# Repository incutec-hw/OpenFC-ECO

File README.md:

# OpenFC-Lite-Mini

Open-source Betaflight flight controller — **20×20 mm**, 6-layer, 3S–6S, built around the RP2354B microcontroller. Compact and low-cost: external RX over UART, microSD blackbox, analog OSD.

> This repository is the **Mini** (20×20). A larger **OpenFC-Lite** (30.5×30.5 mm, bigger pads, more I/O, full-size SD) will be derived from this design once the Mini is finalized.

## At a glance

| | |
|---|---|
| MCU | RP2354B — dual Cortex-M33 @ 150 MHz, 2 MB flash, QFN-80 |
| IMU | 6-axis, SPI0 (LGA-14 footprint — part TBD, see [IMU](#imu)) |
| Blackbox | microSD card slot (TF-021B-H265) on SPI1 |
| OSD | analog, PIO-driven (sync separator + op-amp + SPDT switch) |
| Power | 3S–6S; switchable 10V (VTX/cam) + always-on 5V |
| Size | 20×20 mm, 6-layer |
| RX | external, over UART |
| USB | USB-C, USB-CDC for configuration |

Intentionally omitted to keep it small and cheap: barometer, integrated ELRS receiver, onboard WS2812B LEDs (LED-strip pad only), onboard SPI blackbox flash (microSD instead).

## Status

Rev 1 boards have been received and brought up. The custom Betaflight target builds and flashes; USB enumeration, IMU, SD card blackbox, and the switchable 10V VTX rail are confirmed working on bench. Bring-up of motors, external RX, and the analog OSD chain is in progress. See the [Rev 2 Change List](#rev-2-change-list) for hardware fixes scheduled for the next revision.

## Specifications

### Core
- **MCU:** RP2354B — dual-core ARM Cortex-M33 @ 150 MHz, 2 MB integrated stacked flash, QFN-80
- **IMU:** 6-axis MEMS on SPI0, dedicated 1.8V analog LDO (see [IMU](#imu))
- **Blackbox:** TF-021B-H265 microSD card slot on SPI1
- **USB:** USB-C, USB-CDC for configuration

### Power tree
| Rail | Source | Regulator | Notes |
|---|---|---|---|
| +10V (switchable) | +BATT | LMR51430YFDDCR (U3, 3A) | EN gated by GPIO11 (PINIO1). VTX/cam rail. 4.7µH / 22µF 16V / FB 100k:6.49k → 9.85V. |
| +5V (always-on) | +BATT | LMR51430YFDDCR (U4, 3A) | 4.7µH inductor. |
| +5V (USB/BATT mux) | +5V_BUCK + +5V_USB | TPS2116DRLR (U5) | Auto-selects active source. |
| +3.3V | +5V | LP5912-3.3DRVR (U7) | 500 mA LDO. |
| +1.8V (gyro analog) | +5V | NCV8187AMT180TAG (U6) | Isolated supply for IMU noise rejection. |
| +1.1V (MCU core) | +3.3V | RP2354B internal VREG | — |

### Motor outputs
- 4× PIO-driven DShot outputs (DShot600, bidirectional telemetry supported)
- M1=GPIO31, M2=GPIO30, M3=GPIO29, M4=GPIO28

### Connectors
- **USB-C** — configuration and firmware flashing
- **U8** — 6-pin SMD JST SH digital VTX connector (matches Betaflight standard: +10V/GND/TX/RX/GND/SBUS)
- **P1** — 8-pin TH JST SH ESC harness *(reversed pinout on Rev 1 — must mirror + add telem in Rev 2)*
- **J7/J8** — I2C0 expansion pads (SDA/SCL, with pull-ups to 3.3V)

### Serial / I/O
- **UART0** (GPIO0/1) — digital VTX / MSP DisplayPort
- **UART1** (GPIO22/21) — external serial RX (CRSF/SBUS/etc.)
- **PIO UART0** (GPIO2/3) — software UART, default GPS
- **PIO UART1** (GPIO26/27) — software UART, spare
- **I2C0** (GPIO16/17) — external expansion
- **SPI0** (GPIO18/19/20, CS=GPIO14, INT=GPIO13) — IMU
- **SPI1** (GPIO42/43/44, CS=GPIO46) — microSD blackbox

### Analog inputs
- VBAT sense (GPIO41) — 100k/10k divider, 11:1 ratio, 1k+100nF RC filter
- Current sense (GPIO40) — onboard sense circuit, 1k+100nF RC filter
- RSSI (GPIO45) — 1k+100nF RC filter
- External ADC (GPIO47) — 1k+100nF RC filter

### Additional
- Addressable LED strip output (GPIO23, PIO2)
- Status LED (GPIO12)
- Beeper output (GPIO6)
- 10V rail enable (GPIO11) — exposed as PINIO1/USER1 in firmware

### Analog OSD
- TLV3201AIDBVR (U20) — fast comparator, sync separator on incoming composite video
- TLV9061IDPWR (U19) — op-amp output buffer to the camera signal
- SN74LVC1G3157DTBR (U18) — SPDT analog switch: camera passthrough, black-pixel inject, white-pixel inject
- Driven by RP2354B PIO2 — pixel-level timing for character overlay on PAL/NTSC composite

## IMU

The IMU footprint is LGA-14 (2.5×3 mm), routed with pins 2/3 → GND and pins 10/11 → NC, so it accepts **both TDK (ICM-426xx/456xx) and ST (LSM6D*) families**. Choosing the IMU is a part-population decision, not a layout change.

- **Rev 1** populates **LSM6DSV16XTR** for development only.
- **The Rev 2 IMU is not yet decided** — to be selected after more bench and flight testing.
- Note: TDK parts use a CLKIN line to eliminate sample-timing jitter; ST parts have no CLKIN/SYNC. This couples to the SPI-bus cleanup in the change list below.

## Firmware

A custom Betaflight target (`OPENFC_LITE_MINI_RP2350B`, `MANUFACTURER_ID = OPFC`, `FC_TARGET_MCU = RP2350B`) defines:

- Motor map matching the Rev 1 silkscreen (M1..M4 = GPIO31..GPIO28)
- `USE_SDCARD_SPI` on SPI1 for blackbox
- `USE_PINIO` on GPIO11 for the switchable 10V VTX rail
- FB_OSD framework wired but disabled by default (enable once the analog OSD chain is verified on hardware — note the RP2350B FB_OSD driver is still an open upstream PR stack)

Build (requires a Betaflight checkout with `pico-sdk` and the BF-pinned ARM toolchain):

```sh
make picotool_install
make arm_sdk_install
make CONFIG=OPENFC_LITE_MINI_RP2350B
```

Output is a `.uf2` in `obj/`. Hold BOOTSEL, plug in USB, and drag the UF2 onto the `RP2350` mass-storage drive that mounts.

## PIO Allocation

The RP2350B has 3 PIO blocks × 4 state machines (12 total):

| Block | Function |
|---|---|
| PIO0 | DShot motor output (4 SMs, one per motor) |
| PIO1 | Software UART (PIO UART0 + PIO UART1 — TX and RX programs) |
| PIO2 | LED strip + analog OSD pixel timing |

## Revision History

| Rev | Status | Notes |
|---|---|---|
| **Rev 1** | current | Received and in bench bring-up |
| **Rev 2** | in design | See [Rev 2 Change List](#rev-2-change-list) |

## Rev 2 Change List

Schematic changes for the next revision. **Schematic and board edits are done manually** — this list is the spec to run down.

Legend: 🔧 field swap (value/part only) · 🔌 wiring / topology change · 🔍 decision / investigation · ✅ resolved / done on Rev 2 schematic

### Power
- ✅ **HW-5 — U3/U4 bucks**: LMR51420 (2A) → **LMR51430YFDDCR** (3A, C5219261) — fitted, same SOT-23-6. *Clean the `TI ` prefix out of the MPN field so LCSC/MPN exact-match works for BOM/assembly.*
- ✅ **HW-2 — R30** (10V FB, R29=100k top): 6.8k → **6.49k** (E96, what was in stock). Vout = 0.6·(1 + 100/6.49) = **9.85V** (~1.5% low — fine).
- ✅ **HW-1 — C28** (10V buck output cap): **kept 22µF 16V X5R 0603** (decided against 25V). Voltage margin OK (10V on 16V); DC-bias derates effective C to ~7–11µF, which with the 4.7µH inductor raises 10V ripple but is acceptable for a **digital** VTX rail.
- ✅ **HW-3 — L2/L3 inductors**: **both rails = 4.7µH (XRTC303020D4R7MBCA)** (decided against 10µH on L2). 10V ripple ≈1.17A p-p at 6S; peak well under the 3A part. *Verify the inductor Isat ≥ ~4A.*
- ✅ **HW-8 — U6 gyro LDO**: **kept NCV8187AMT180TAG** (300 mA) for its PSRR — electrically ample (gyro analog is single-digit mA). ⚠️ BF §3.1.2 lists ≥500 mA; confirm whether that's hard-gated at submission. Low stock → consign if needed.

### MCU / USB (per Raspberry Pi RP2350 datasheet)
- ✅ **R12/R13/R14**: **no change** — keep all at 30Ω. USB FS is impedance-tolerant (30 vs 27Ω inaudible to enumeration); R14 (VREG_AVDD RC filter) 30 vs 33Ω is negligible. Single resistor value = better DFM.
- 🔍 **D1 — USB ESD (USBLC6-2P6)**: removed on current schematic. ⚠️ **Recommend restoring.** USB is the most-handled / most-exposed interface; the RP2354B PHY isn't rated for system-level (IEC 61000-4-2 8kV) ESD, and the part is tiny/cheap/low-C. The "inconsistency" argument favors adding TVS to the *other* exposed I/O, not stripping USB. **Pending final call.**

### LEDs
- ✅ All indicator LEDs **0201 → 0402** (0201 too fragile — broke during nut install).
- ✅ **HW-4 — D2** (LED0 status, GPIO12): green → **blue** (XL-1005UBC, C22355736). BF §3.1.4.6.
- ✅ **LED series resistors recalculated for ~1mA** (greens = XL-1005UGC, C965793). Vf@1mA estimated: blue ≈2.75V, green ≈2.6V.

  | LED | Color | Source | Old R | **New R (E24)** | I |
  |---|---|---|---|---|---|
  | D2 (LED0) | Blue | GPIO12 (~3.3V) | 30R | **510Ω** | ~1.0mA |
  | D7 | Green | +3.3V | 30R | **680Ω** | ~1.0mA |
  | D5 | Green | +5V (5V_BUCK) | 200R | **2.4kΩ** | ~1.0mA |
  | D4 | Green | +10V | 470R | **7.5kΩ** | ~1.0mA |

  D2/D7 sit on 3.3V with low headroom → current is Vf-sensitive; if dim, D2→430Ω, D7→560Ω. Optional: D2→330Ω (~2mA) for daylight pre-arm visibility.

### Signals / connectivity (wiring — manual)
- 🔌 **SPI0 cleanup**: group **GYRO_CS** into the SPI bus (with SCK/MOSI/MISO); drop the IMU **CLKIN/SYNC** net (GPIO15) — ST gyros have no SYNC. Same regroup for **FLASH_CS** (SD). ⚠️ If a TDK IMU is chosen, CLKIN is useful — couple to the IMU decision.
- ✅ **SBUS inverter removed** (GPIO9). Confirmed safe: BF PICO inverts at the RP2350 pad IO-mux (`gpio_set_inover/outover(GPIO_OVERRIDE_INVERT)`), auto-set for SBUS, works on native + PIO UARTs. The SBUS line wires straight to a UART/PIO-UART **RX** GPIO; firmware inverts.
- 🔌 **HW-6 — ESC connector P1**: mirror reversed pinout **+ add telemetry pin** (BF 8-pin: Current = pin 3, Telem = pin 4). **Safety-critical** — current pinout shorts VBAT to a GPIO on a standard BF harness.
- 🔌 **HW-7** — Add **battery reverse-polarity protection** (PMOS RPP).
- ✅ **HW-11 — Beeper**: done — **N-MOS low-side switch** (Q2 DMN1150UFB-7B, R20 1k gate, R23 100k pulldown, BEEPER = GPIO6). Better than the NPN spec. *Verify: (1) flyback diode is across the buzzer (cathode → +supply, anode → drain), not just the FET body diode; (2) DMN1150UFB-7B is logic-level (turns on hard at 3.3V).*
- 🔌 **SD card**: wire compatible with both SPI and SDIO; use SPI for now (see SDIO decision below).

### Decisions / investigations
- 🔍 **IMU** — undecided for Rev 2; see [IMU](#imu).
- ✅ **U5 power MUX** — **TPS2116DRLR** confirmed (auto-select USB/BATT).
- ✅ **SDIO on Pico** — **stay on SPI.** Betaflight PICO supports SD blackbox over **SPI only** (PR #14567); no SDIO under `src/platform/PICO/`, no open PR. SDIO would give ~10× throughput (~25 MB/s vs ~2 MB/s — needed for 4kHz+ full-field logging) but requires a 4-bit HW bus *and* firmware that doesn't exist. SPI1 microSD is correct.
- ✅ **CRIT-2 — motor order**: keep reversed silk (eases routing); **resolve in the BF target's DShot motor resource order** so M1–M4 map to the pads. Documented in the target.
- 🔍 **CRIT-3 — FB_OSD upstream**: the RP2350B analog-OSD driver PR stack (#14882) is still open; no flyable upstream binary yet. Track before tape-out.
- ✅ **SWD connector** — **not adding.** RP2354B flashes over USB (UF2/BOOTSEL); SWD is only for live debug. Optional test pads cost nothing but no connector needed.

## Repository Structure

```
OpenFC-Lite-Mini/
├── README.md
├── LICENSE
├── hardware/                ← KiCad 9 project, libraries, and production files
│   ├── OpenFC.kicad_pro     ← Project file
│   ├── OpenFC.kicad_pcb     ← PCB layout
│   ├── OpenFC.kicad_sch     ← Top-level schematic (hierarchical)
│   ├── *.kicad_sch          ← Sub-sheets
│   ├── lib.kicad_sym        ← Project-local symbol library
│   ├── lib.pretty/          ← Project-local footprint library
│   ├── lib.3dshapes/        ← Project-local 3D models
│   ├── production/          ← JLCPCB production exports, per revision
│   └── tools/               ← Analysis scripts (Python, kicad-skip / pcbnew API)
└── images/                  ← Board renders
```

All symbol, footprint, and 3D model libraries are project-local — no external library setup required.

## Schematic Hierarchy

- `OpenFC.kicad_sch` — top-level
- `rp2350a.kicad_sch` — RP2354B microcontroller and supporting circuitry
- `power.kicad_sch` — power supply and regulation (10V buck, 5V buck, 3.3V/1.8V LDOs, 5V mux)
- `imu.kicad_sch` — 6-axis IMU on SPI0 (LGA-14 2.5×3 footprint; Rev 1 populates LSM6DSV16XTR for dev — see [IMU](#imu))
- `osd.kicad_sch` — analog OSD chain (TLV3201 sync sep + TLV9061 buffer + SN74LVC1G3157 switch)
- `blackbox.kicad_sch` — TF-021B-H265 microSD card slot
- `pads.kicad_sch` — solder pads and connectors

## License

Hardware licensed under [CERN-OHL-S-2.0](https://ohwr.org/cern_ohl_s_v2.txt). See [LICENSE](LICENSE) for details.

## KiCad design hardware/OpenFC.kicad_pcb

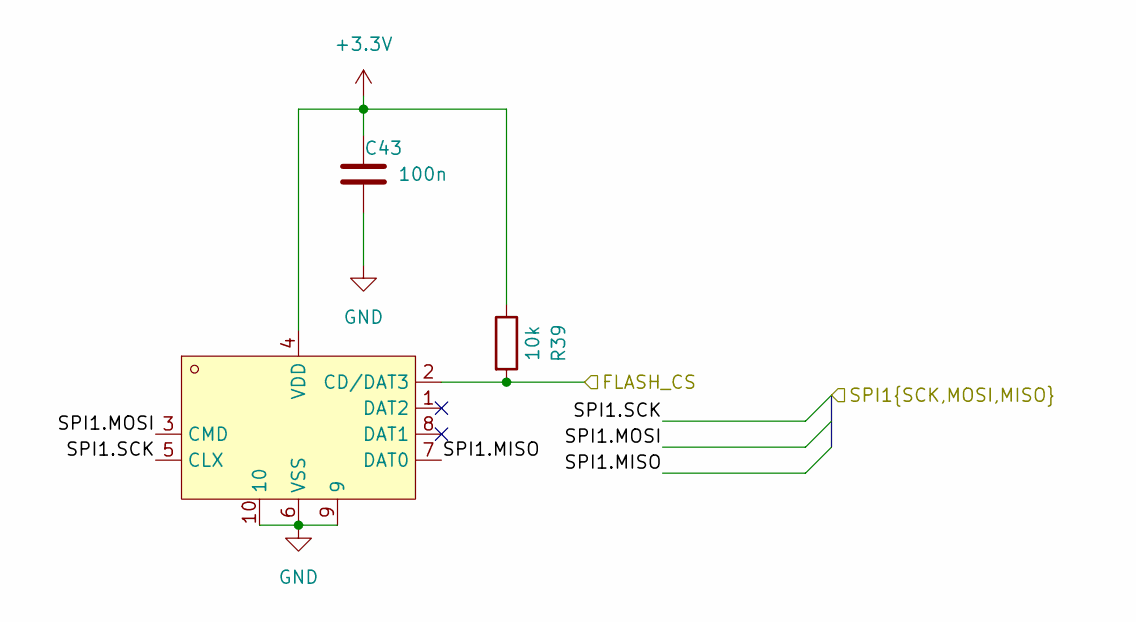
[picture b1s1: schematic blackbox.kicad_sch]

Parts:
C43: 100n; C_0201_0603Metric; MPN GRM033R61E104KE14D; LCSC C76939
Card1: TF-021B-H265; TF-SMD_TF-021B-H265; LCSC C498185
R39: 10k; R_0201_0603Metric; MPN RC0201FR-0710KL; LCSC C106225

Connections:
/BLACKBOX/FLASH_CS: Card1.2 (CD/DAT3), R39.2; also elsewhere on the board
/BLACKBOX/SPI1.MISO: Card1.7 (DAT0); also elsewhere on the board
/BLACKBOX/SPI1.MOSI: Card1.3 (CMD); also elsewhere on the board
/BLACKBOX/SPI1.SCK: Card1.5 (CLX); also elsewhere on the board
GND: C43.2, Card1.6 (VSS), Card1.9, Card1.10; also elsewhere on the board

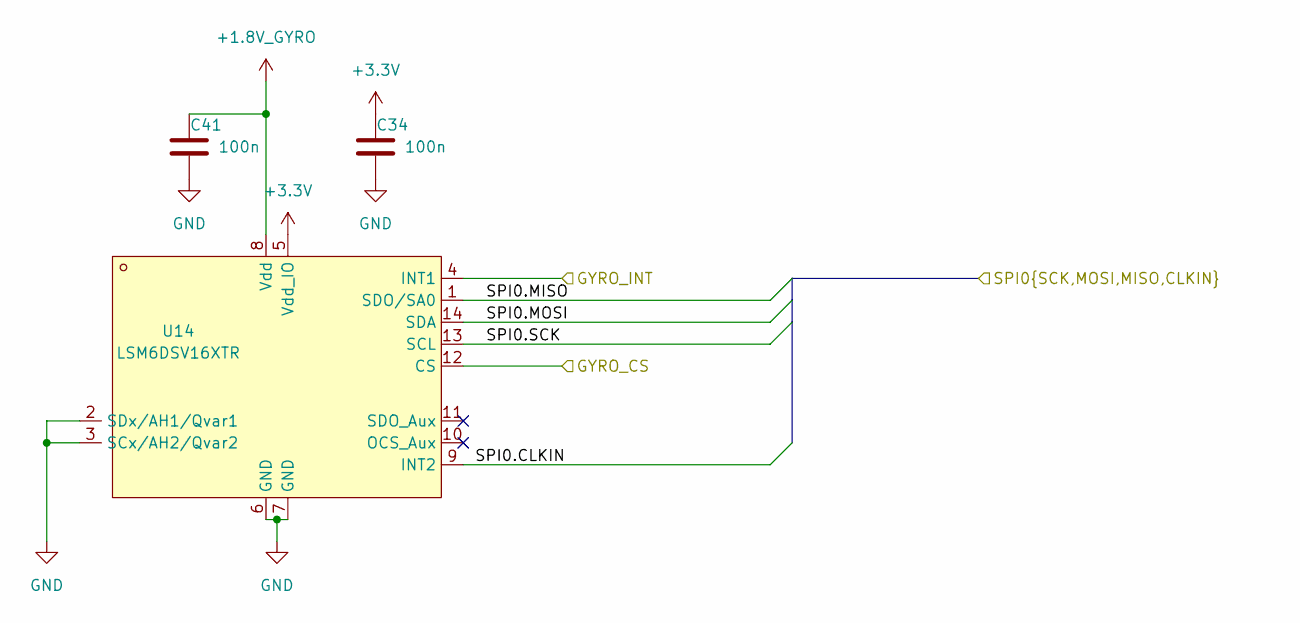
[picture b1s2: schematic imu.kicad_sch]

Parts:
C34, C41: 100n; C_0201_0603Metric; MPN GRM033R61E104KE14D; LCSC C76939
U14: LSM6DSV16XTR; LGA-14_L3.0-W2.5-P0.50-BR; MPN LSM6DSV16XTR; LCSC Part C5267406

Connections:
GND: C34.2, C41.2, U14.2 (SDx/AH1/Qvar1), U14.3 (SCx/AH2/Qvar2), U14.6 (GND), U14.7 (GND); also elsewhere on the board

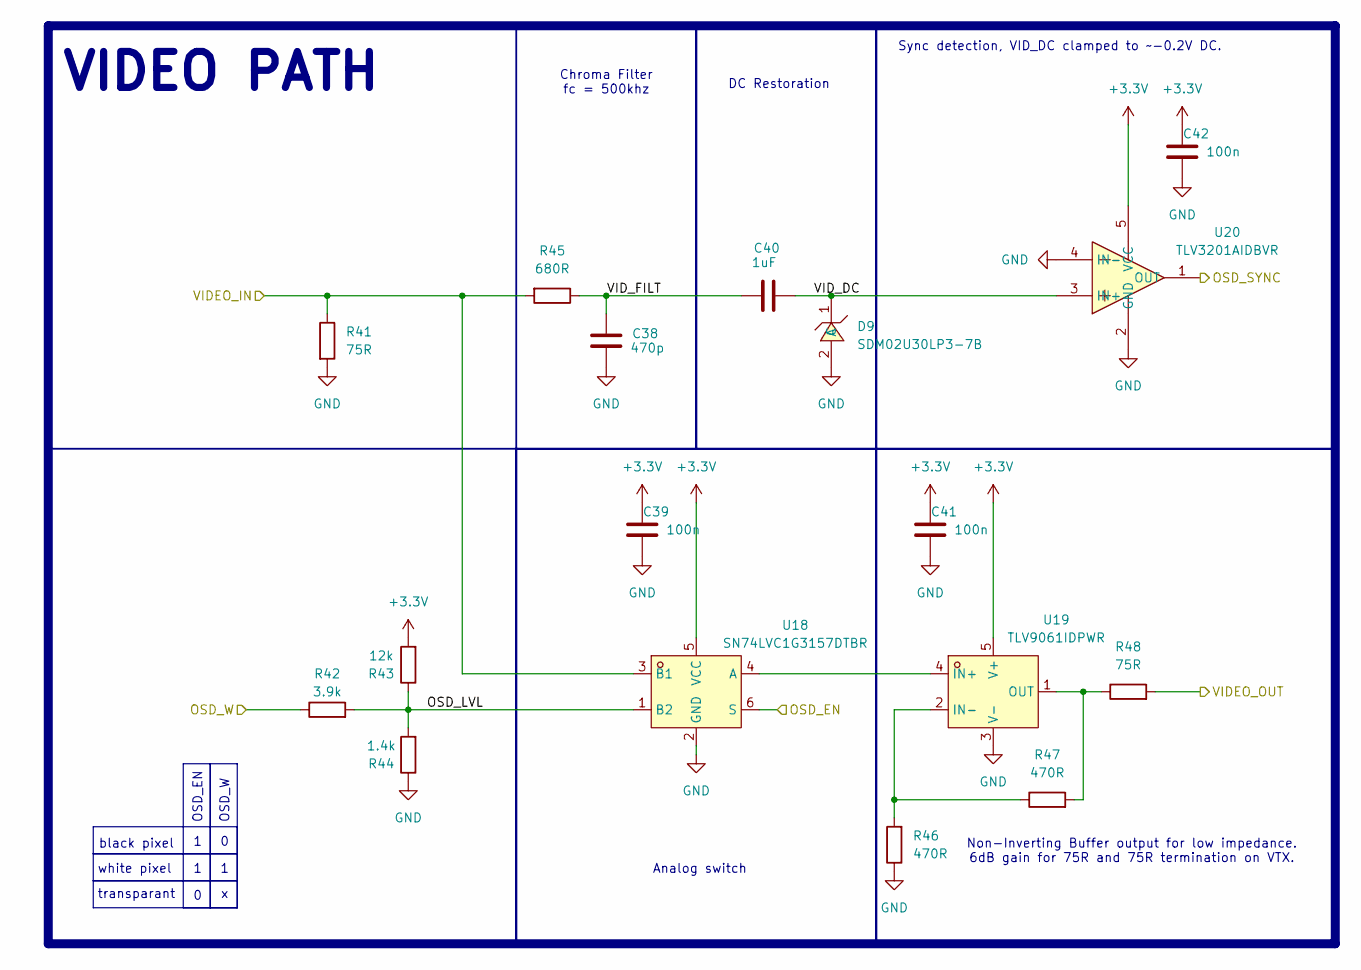
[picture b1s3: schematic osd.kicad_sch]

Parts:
C38: 470p; C_0201_0603Metric; MPN CC0201JRX7R9BB471; LCSC C526944
C39, C41, C42: 100n; C_0201_0603Metric; MPN GRM033R60J104KE19D; LCSC C76928
C40: 1uF; C_0402_1005Metric; MPN CL05A105KA5NQNC; LCSC C52923
D9: SDM02U30LP3-7B; X3-DFN0603-2_L0.6-W0.3-RD; MPN SDM02U30LP3-7B; LCSC Part C151629
R41, R48: 75R; R_0201_0603Metric; MPN RC0201FR-0775RL; LCSC C274878
R42: 3.9k; R_0201_0603Metric; MPN RC0201FR-073K9L; LCSC C273280
R43: 12k; R_0201_0603Metric; MPN 0201WMF1202TEE; LCSC C270363
R44: 1.4k; R_0201_0603Metric; MPN 0201WMF1401TEE; LCSC C423739
R45: 680R; R_0201_0603Metric; MPN 0201WMF6800TEE; LCSC C473509
R46, R47: 470R; R_0201_0603Metric; MPN 0201WMF4700TEE; LCSC C473464
U18: SN74LVC1G3157DTBR; X2SON-6_L1.0-W0.8-BL; MPN SN74LVC1G3157DTBR; LCSC Part C2673087
U19: TLV9061IDPWR; X2SON-4_L0.8-W0.8-P0.48-TL-DPW; MPN TLV9061IDPWR; LCSC Part C2057878
U20: TLV3201AIDBVR; SOT-23-5_L3.0-W1.7-P0.95-LS2.8-BR; MPN TLV3201AIDBVR; LCSC Part C105188

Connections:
/OSD/OSD_EN: U18.6 (S); also elsewhere on the board
/OSD/OSD_LVL: R42.2, R43.1, R44.2, U18.1 (B2)
/OSD/OSD_W: R42.1; also elsewhere on the board
/OSD/VIDEO_IN: R41.1, R45.2, U18.3 (B1); also elsewhere on the board
/OSD/VIDEO_OUT: R48.2; also elsewhere on the board
/OSD/VID_DC: C40.2, D9.1 (C), U20.3 (IN+)
/OSD/VID_FILT: C38.1, C40.1, R45.1
GND: C38.2, C39.2, C41.2, C42.2, D9.2 (A), R41.2, R44.1, R46.1, U18.2 (GND), U19.3 (V-), U20.2 (GND), U20.4 (IN-); also elsewhere on the board
unnamed: U18.4 (A), U19.4 (IN+)
unnamed: R46.2, R47.1, U19.2 (IN-)
unnamed: R47.2, R48.1, U19.1 (OUT)

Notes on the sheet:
Sync detection, VID_DC clamped to ~-0.2V DC.
Non-Inverting Buffer output for low impedance. 6dB gain for 75R and 75R termination on VTX.
VIDEO PATH
Analog switch
black pixel
white pixel
OSD_W
DC Restoration
Chroma Filter fc = 500khz
OSD_EN
transparant

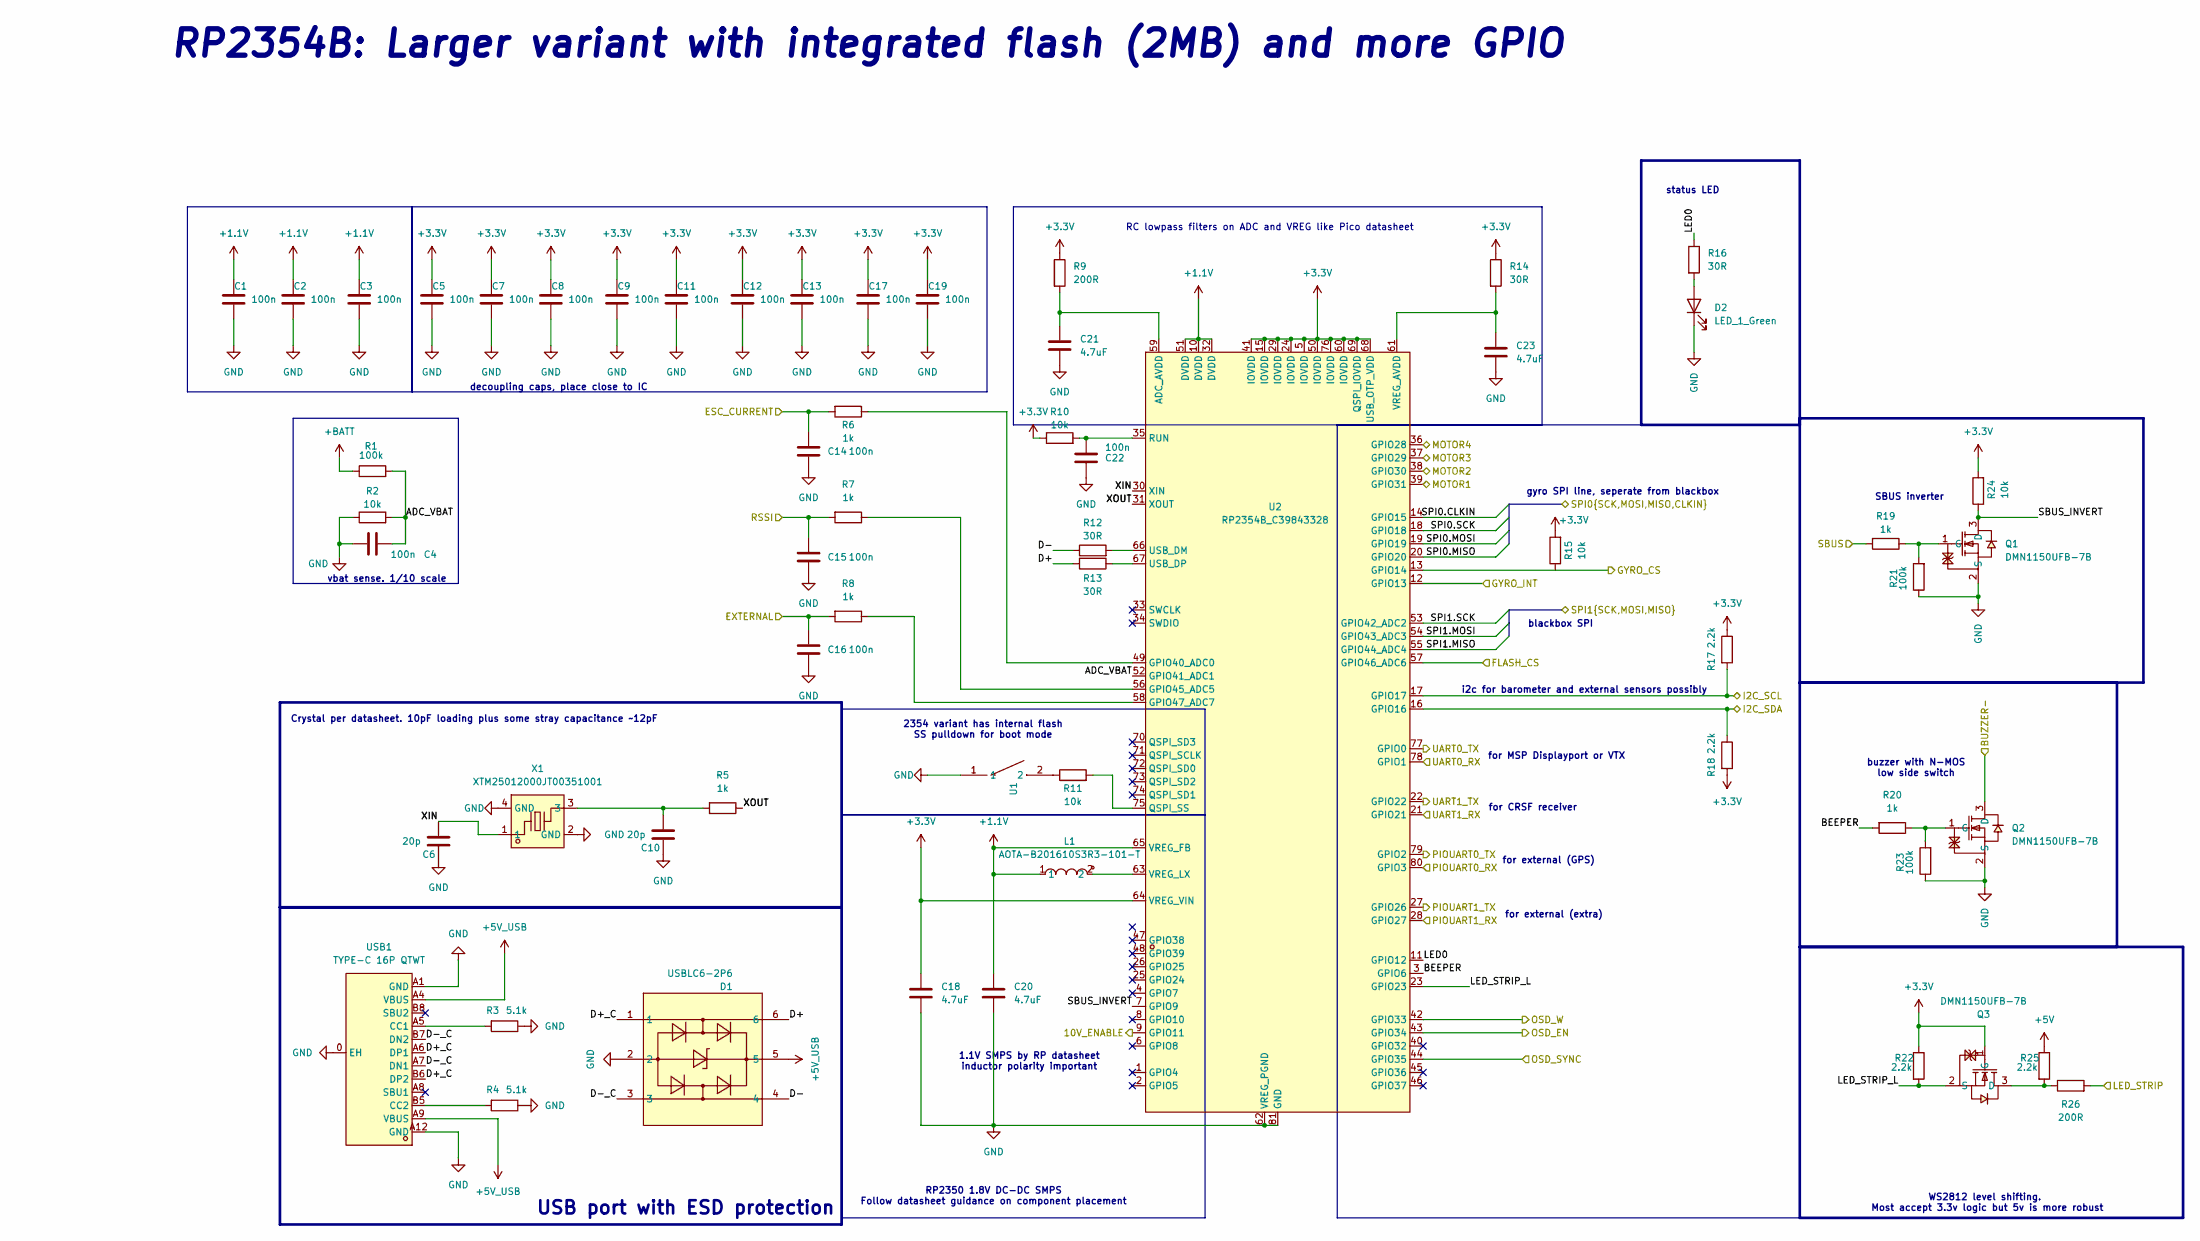
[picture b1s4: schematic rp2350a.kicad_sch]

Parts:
C1, C2, C3, C4, C5, C7, C8, C9, C11, C12, C13, C14, C15, C16, C17, C19, C22: 100n; C_0201_0603Metric; MPN GRM033R61E104KE14D; LCSC C76939
C6, C10: 20p; C_0201_0603Metric; MPN GRM0335C1H200JA01D; LCSC C76923
C18, C20, C21, C23: 4.7uF; C_0402_1005Metric; MPN CL05A475MP5NRNC; LCSC C23733
D1: USBLC6-2P6; SOT-666; MPN USBLC6-2P6; LCSC Part C15999
D2: LED_1_Green; LED_0201_0603Metric; MPN XL-0201UGC; LCSC C3646922
L1: AOTA-B201610S3R3-101-T; IND-SMD_L2.0-W1.6_AOTA-B201610S3R3-101-T; MPN AOTA-B201610S3R3-101-T; LCSC Part C42411119
Q1, Q2, Q3: DMN1150UFB-7B; DFN-3L_L1.0-W0.6-P0.65-BR; MPN DMN1150UFB-7B; LCSC Part C459538
R1, R21, R23: 100k; C_0201_0603Metric; MPN 0201WMF1003TEE; LCSC C270364
R2, R10, R11, R15, R24: 10k; C_0201_0603Metric; MPN RC0201FR-0710KL; LCSC C106225
R3, R4: 5.1k; C_0201_0603Metric; MPN 0201WMF5101TEE; LCSC C270344
R5, R6, R7, R8, R19, R20: 1k; C_0201_0603Metric; MPN 0201WMF1001TEE; LCSC C270365
R9, R26: 200R; C_0201_0603Metric; MPN 0201WMF2000TEE; LCSC C270359
R12, R13, R14, R16: 30R; C_0201_0603Metric; MPN NQ01WMJ0300TEE; LCSC C778391
R17, R18, R22, R25: 2.2k; C_0201_0603Metric; MPN RC0201FR-072K2L; LCSC C142018
U1: TS2306A 240GF MSM 9_C2976675; SW-SMD_4P-L3.0-W2.0-P0.85-LS3.5; MPN TS2306A 240gf MSM 9; LCSC Part C2976675
U2: RP2354B_C39843328; QFN-80_L10.0-W10.0-P0.40-TL-EP3.4; MPN RP2354B; LCSC Part C39843328
USB1: TYPE-C 16P QTWT; USB-TYPE-C-SMD_TYPE-C-16P-QTWT; MPN TYPE-C 16P QTWT; LCSC Part C5187472
X1: XTM25012000JT00351001; CRYSTAL-SMD_4P-L2.5-W2.0-BL-A; MPN XTM25012000JT00351001; LCSC Part C37635340

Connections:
+1.1V: C1.1, C2.1, C3.1, C20.1, L1.1, U2.10 (DVDD), U2.32 (DVDD), U2.51 (DVDD), U2.65 (VREG_FB)
+5V: R25.1; also elsewhere on the board
+5V_USB: D1.5, USB1.A4 (VBUS), USB1.A9 (VBUS); also elsewhere on the board
+BATT: R1.1; also elsewhere on the board
/BLACKBOX/FLASH_CS: U2.57 (GPIO46_ADC6); also elsewhere on the board
/BLACKBOX/SPI1.MISO: U2.55 (GPIO44_ADC4); also elsewhere on the board
/BLACKBOX/SPI1.MOSI: U2.54 (GPIO43_ADC3); also elsewhere on the board
/BLACKBOX/SPI1.SCK: U2.53 (GPIO42_ADC2); also elsewhere on the board
/I2C_SCL: R17.2, U2.17 (GPIO17); also elsewhere on the board
/I2C_SDA: R18.1, U2.16 (GPIO16); also elsewhere on the board
/IMU/GYRO_CS: R15.1, U2.13 (GPIO14); also elsewhere on the board
/IMU/GYRO_INT: U2.12 (GPIO13); also elsewhere on the board
/IMU/SPI0.CLKIN: U2.14 (GPIO15); also elsewhere on the board
/IMU/SPI0.MISO: U2.20 (GPIO20); also elsewhere on the board
/IMU/SPI0.MOSI: U2.19 (GPIO19); also elsewhere on the board
/IMU/SPI0.SCK: U2.18 (GPIO18); also elsewhere on the board
/LED: R26.2; also elsewhere on the board
/OSD/OSD_EN: U2.2 (GPIO5); also elsewhere on the board
/OSD/OSD_W: U2.1 (GPIO4); also elsewhere on the board
/PADS/ADC2: C16.2, R8.2; also elsewhere on the board
/PADS/BUZZER-: Q2.3 (D); also elsewhere on the board
/PADS/CURRENT: C14.2, R6.2; also elsewhere on the board
/PADS/DIGITAL_RX: U2.78 (GPIO1); also elsewhere on the board
/PADS/DIGITAL_TX: U2.77 (GPIO0); also elsewhere on the board
/PADS/M1: U2.39 (GPIO31); also elsewhere on the board
/PADS/M2: U2.38 (GPIO30); also elsewhere on the board
/PADS/M3: U2.37 (GPIO29); also elsewhere on the board
/PADS/M4: U2.36 (GPIO28); also elsewhere on the board
/PADS/PIOUART0_RX: U2.80 (GPIO3); also elsewhere on the board
/PADS/PIOUART0_TX: U2.79 (GPIO2); also elsewhere on the board
/PADS/PIOUART1_RX: U2.28 (GPIO27); also elsewhere on the board
/PADS/PIOUART1_TX: U2.27 (GPIO26); also elsewhere on the board
/PADS/RSSI: C15.2, R7.2; also elsewhere on the board
/PADS/SBUS: R19.2; also elsewhere on the board
/POWER/10V_ENABLE: U2.9 (GPIO11); also elsewhere on the board
/RP2350A/ADC_VBAT: C4.2, R1.2, R2.2, U2.52 (GPIO41_ADC1)
/RP2350A/D+: D1.6, R13.2
/RP2350A/D+_C: D1.1, USB1.A6 (DP1), USB1.B6 (DP2)
/RP2350A/D-: D1.4, R12.1
/RP2350A/D-_C: D1.3, USB1.A7 (DN1), USB1.B7 (DN2)
/RP2350A/LED0: R16.1, U2.11 (GPIO12)
/RP2350A/LED_STRIP_L: Q3.2 (S), R22.2, U2.23 (GPIO23)
/RP2350A/SBUS_INVERT: Q1.3 (D), R24.1, U2.7 (GPIO9)
/RP2350A/XIN: C6.2, U2.30 (XIN), X1.1
/RP2350A/XOUT: R5.1, U2.31 (XOUT)
/UART1_RX: U2.21 (GPIO21); also elsewhere on the board
/UART1_TX: U2.22 (GPIO22); also elsewhere on the board
GND: C1.2, C2.2, C3.2, C4.1, C5.2, C6.1, C7.2, C8.2, C9.2, C10.1, C11.2, C12.2, C13.2, C14.1, C15.1, C16.1, C17.2, C18.2, C19.2, C20.2, C21.2, C22.1, C23.2, D1.2, D2.1 (K), Q1.2 (S), Q2.2 (S), R2.1, R3.1, R4.1, R21.1, R23.1, U1.1, U2.62 (VREG_PGND), U2.81 (GND), USB1.0 (EH), USB1.A1 (GND), USB1.A12 (GND), X1.2 (GND), X1.4 (GND); also elsewhere on the board
unnamed: C10.2, R5.2, X1.3
unnamed: D2.2 (A), R16.2
unnamed: Q1.1 (G), R19.1, R21.2
unnamed: Q2.1 (G), R20.1, R23.2
unnamed: Q3.3 (D), R25.2, R26.1
unnamed: R11.1, U1.2
unnamed: C21.1, R9.2, U2.59 (ADC_AVDD)
unnamed: R6.1, U2.49 (GPIO40_ADC0)
unnamed: R7.1, U2.56 (GPIO45_ADC5)
unnamed: R8.1, U2.58 (GPIO47_ADC7)
unnamed: R11.2, U2.75 (QSPI_SS)
unnamed: C22.2, R10.2, U2.35 (RUN)
unnamed: R12.2, U2.66 (USB_DM)
unnamed: R13.1, U2.67 (USB_DP)
unnamed: C23.1, R14.2, U2.61 (VREG_AVDD)
unnamed: L1.2, U2.63 (VREG_LX)
unnamed: R3.2, USB1.A5 (CC1)
unnamed: R4.2, USB1.B5 (CC2)

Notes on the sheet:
vbat sense. 1/10 scale
RP2354B: Larger variant with integrated flash (2MB) and more GPIO
blackbox SPI
buzzer with N-MOS low side switch
for MSP Displayport or VTX
2354 variant has internal flash SS pulldown for boot mode
RP2350 1.8V DC-DC SMPS Follow datasheet guidance on component placement
for CRSF receiver
gyro SPI line, seperate from blackbox
decoupling caps, place close to IC
for external (extra)
status LED
Crystal per datasheet. 10pF loading plus some stray capacitance ~12pF
for external (GPS)
i2c for barometer and external sensors possibly
SBUS inverter
RC lowpass filters on ADC and VREG like Pico datasheet
WS2812 level shifting. Most accept 3.3v logic but 5v is more robust
USB port with ESD protection
1.1V SMPS by RP datasheet inductor polarity important

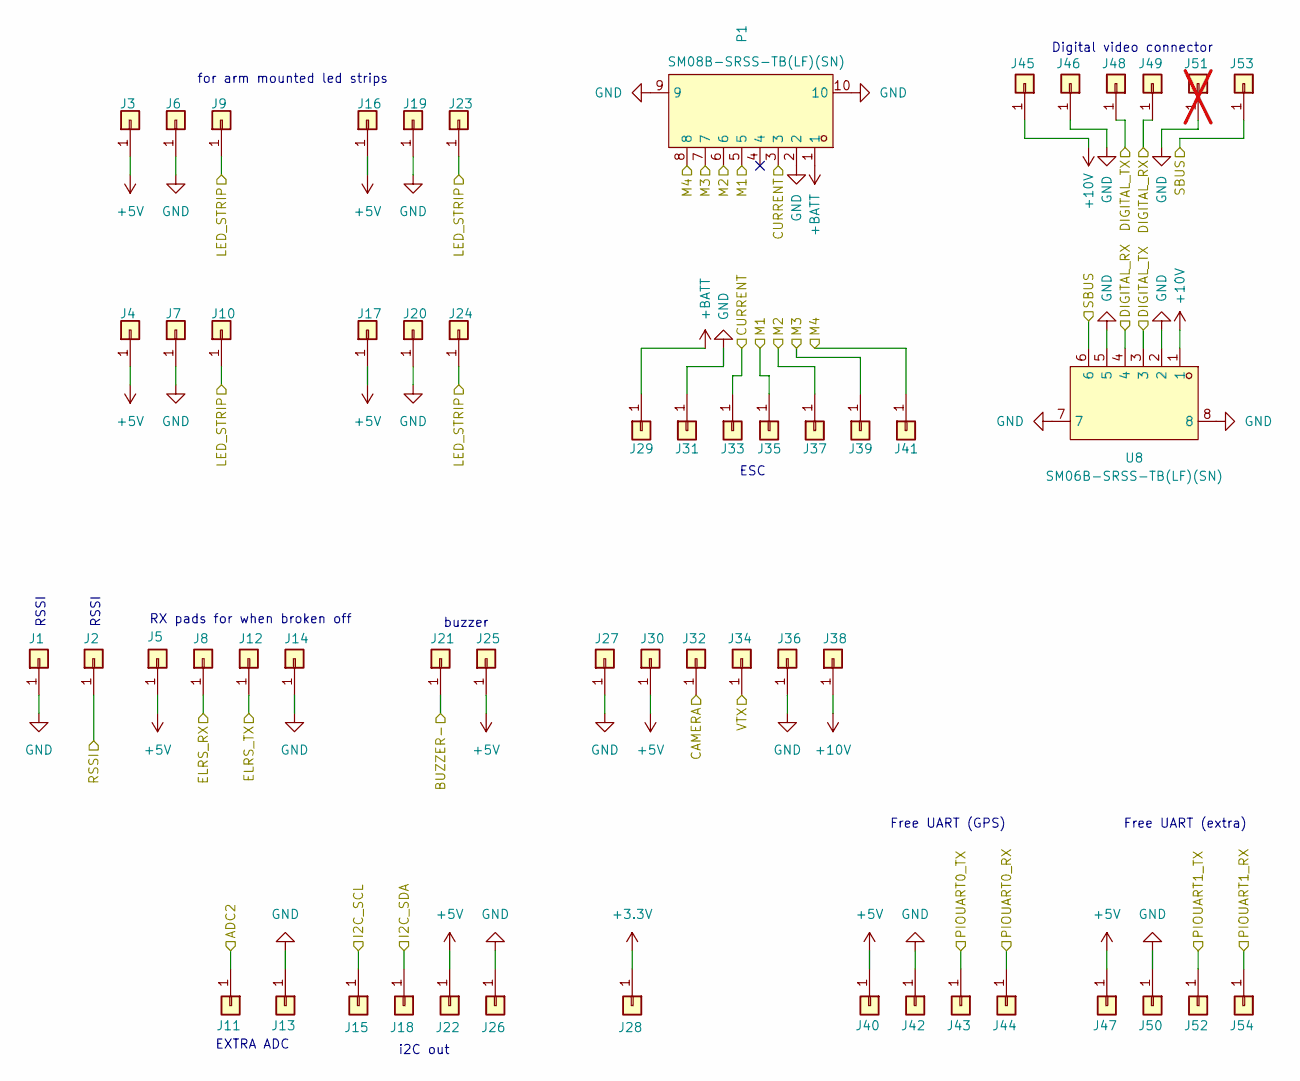
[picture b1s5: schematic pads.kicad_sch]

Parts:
J1, J2, J3, J4, J5, J6, J7, J8, J9, J10, J11, J12, J13, J14, J15, J16, J17, J18, J19, J20, J21, J22, J23, J24, J25, J26, J27, J28, J29, J30, J31, J32, J33, J34, J35, J36, J37, J38, J39, J40, J41, J42, J43, J44, J45, J46, J47, J48, J49, J50, J52, J53, J54: 5V; small_pad
J51: 5V; small_pad; not fitted
P1: SM08B-SRSS-TB(LF)(SN); CONN-TH_SM08B-SRSS-TB-LF-SN; MPN SM08B-SRSS-TB(LF)(SN); LCSC Part C160407
U8: SM06B-SRSS-TB(LF)(SN); CONN-SMD_SM06B-SRSS-TB-LF-SN; MPN SM06B-SRSS-TB(LF)(SN); LCSC Part C160405

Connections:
+5V: J3.1, J4.1 (Pin_1_1), J5.1 (Pin_1_1), J16.1, J17.1, J22.1 (Pin_1_1), J25.1 (Pin_1_1), J30.1 (Pin_1_1), J40.1 (Pin_1_1), J47.1 (Pin_1_1); also elsewhere on the board
+10V: J38.1 (Pin_1_1), J45.1 (Pin_1_1), U8.1; also elsewhere on the board
+BATT: J29.1 (Pin_1_1), P1.1; also elsewhere on the board
/I2C_SCL: J15.1 (Pin_1_1); also elsewhere on the board
/I2C_SDA: J18.1 (Pin_1_1); also elsewhere on the board
/LED: J9.1, J10.1 (Pin_1_1), J23.1, J24.1; also elsewhere on the board
/OSD/VIDEO_IN: J32.1 (Pin_1_1); also elsewhere on the board
/OSD/VIDEO_OUT: J34.1 (Pin_1_1); also elsewhere on the board
/PADS/ADC2: J11.1 (Pin_1_1); also elsewhere on the board
/PADS/BUZZER-: J21.1 (Pin_1_1); also elsewhere on the board
/PADS/CURRENT: J33.1 (Pin_1_1), P1.3; also elsewhere on the board
/PADS/DIGITAL_RX: J49.1 (Pin_1_1), U8.4; also elsewhere on the board
/PADS/DIGITAL_TX: J48.1 (Pin_1_1), U8.3; also elsewhere on the board
/PADS/M1: J35.1 (Pin_1_1), P1.5; also elsewhere on the board
/PADS/M2: J37.1 (Pin_1_1), P1.6; also elsewhere on the board
/PADS/M3: J39.1 (Pin_1_1), P1.7; also elsewhere on the board
/PADS/M4: J41.1 (Pin_1_1), P1.8; also elsewhere on the board
/PADS/PIOUART0_RX: J44.1 (Pin_1_1); also elsewhere on the board
/PADS/PIOUART0_TX: J43.1 (Pin_1_1); also elsewhere on the board
/PADS/PIOUART1_RX: J54.1 (Pin_1_1); also elsewhere on the board
/PADS/PIOUART1_TX: J52.1 (Pin_1_1); also elsewhere on the board
/PADS/RSSI: J2.1 (Pin_1_1); also elsewhere on the board
/PADS/SBUS: J53.1 (Pin_1_1), U8.6; also elsewhere on the board
/UART1_RX: J8.1 (Pin_1_1); also elsewhere on the board
/UART1_TX: J12.1 (Pin_1_1); also elsewhere on the board
GND: J1.1 (Pin_1_1), J6.1, J7.1 (Pin_1_1), J13.1 (Pin_1_1), J14.1 (Pin_1_1), J19.1, J20.1, J26.1 (Pin_1_1), J27.1 (Pin_1_1), J31.1 (Pin_1_1), J36.1 (Pin_1_1), J42.1 (Pin_1_1), J46.1 (Pin_1_1), J50.1 (Pin_1_1), J51.1, P1.2, P1.9, P1.10, U8.2, U8.5, U8.7, U8.8; also elsewhere on the board

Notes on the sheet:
RSSI
Free UART (GPS)
i2C out
Free UART (extra)
buzzer
RX pads for when broken off
ESC
Digital video connector
EXTRA ADC
for arm mounted led strips

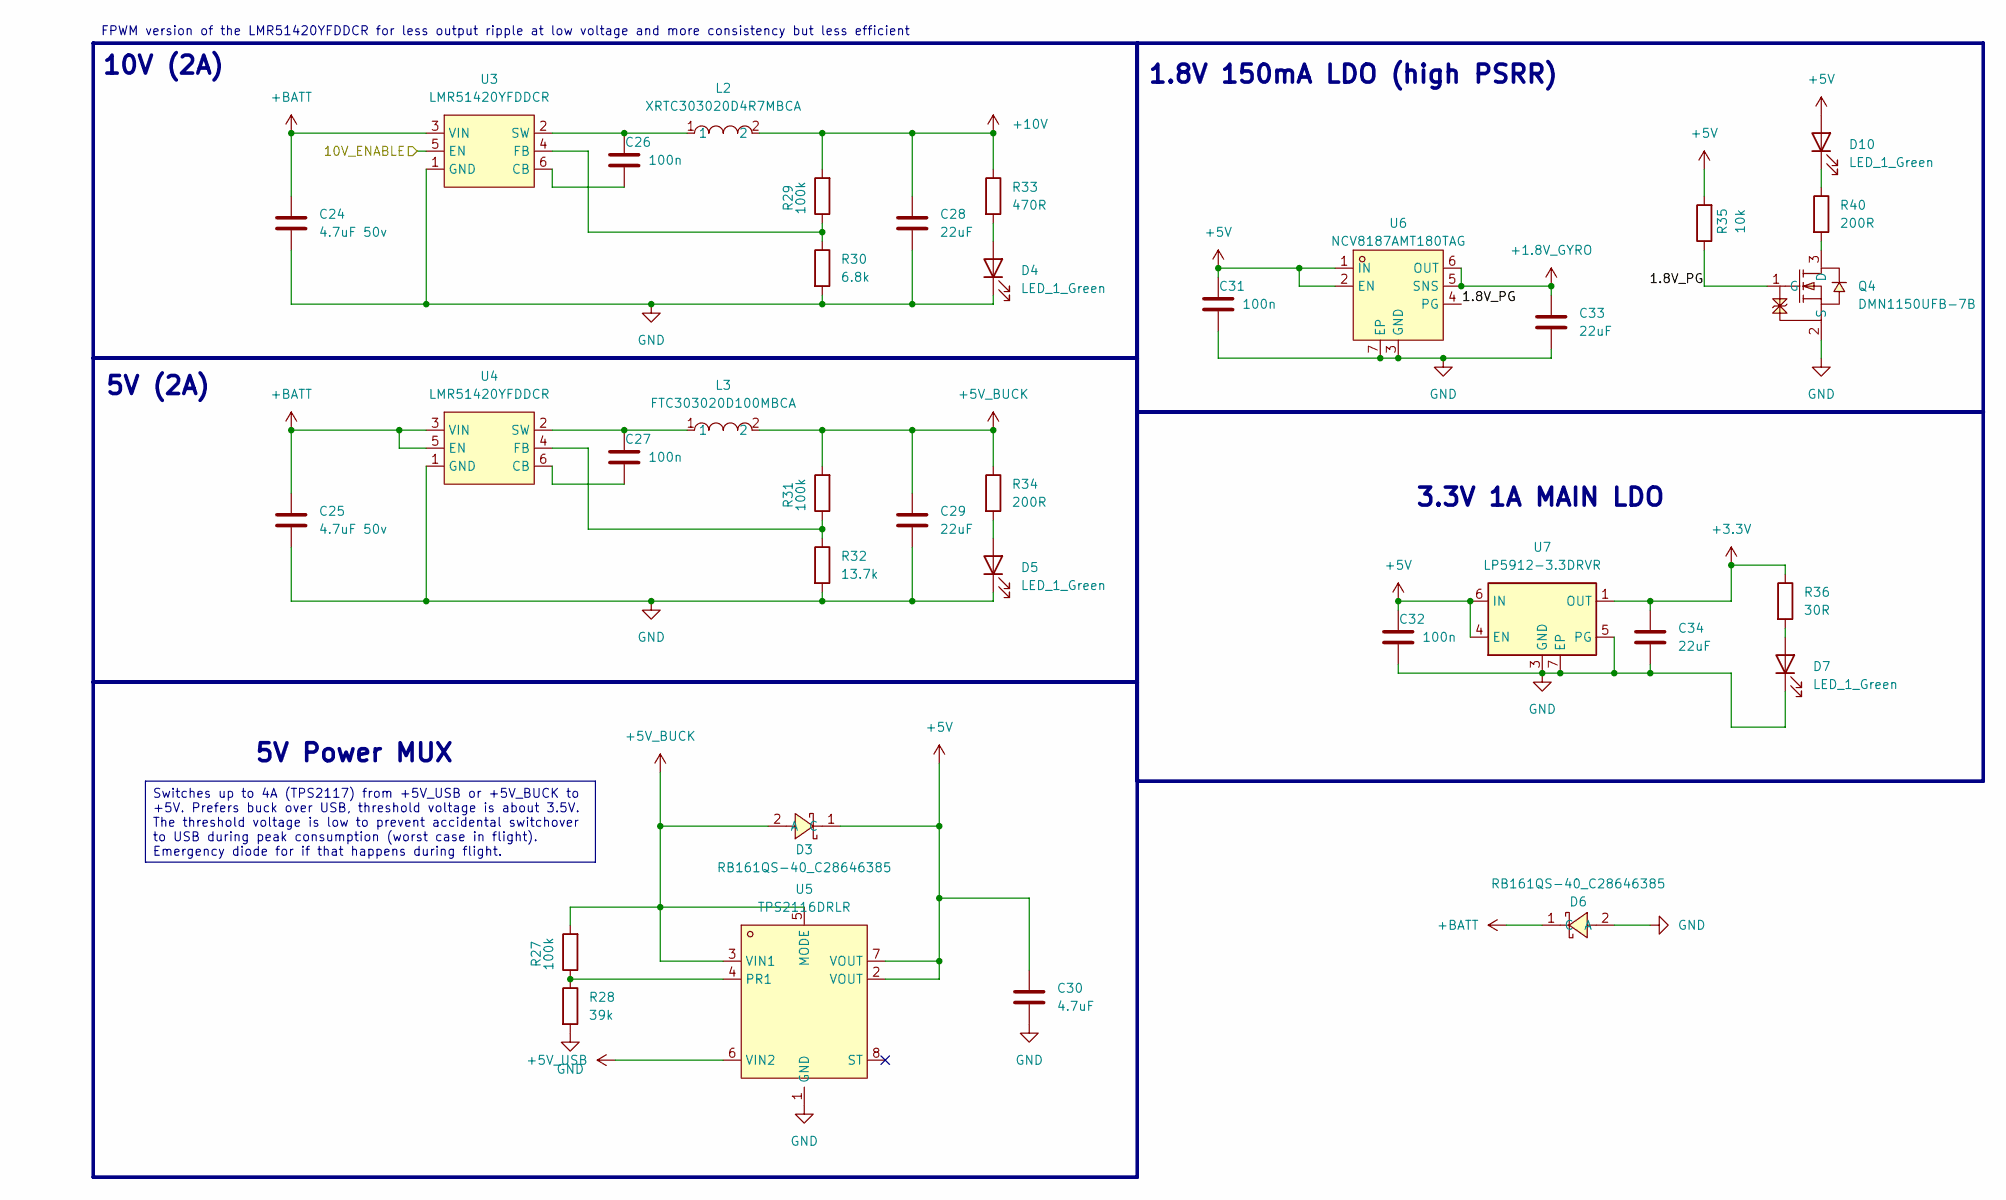
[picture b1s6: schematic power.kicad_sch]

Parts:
C24, C25: 4.7uF 50v; C_0805_2012Metric; MPN CL21A475KBQNNNE; LCSC C98192
C26, C27, C31, C32: 100n; C_0201_0603Metric; MPN GRM033R61E104KE14D; LCSC C76939
C28, C29: 22uF; C_0603_1608Metric; MPN CL10A226MO7JZNC; LCSC C2762594
C30: 4.7uF; C_0402_1005Metric; MPN CL05A475MP5NRNC; LCSC C23733
C33, C34: 22uF; C_0402_1005Metric; MPN CL05A226MQ5QUNC; LCSC C105226
D3, D6: RB161QS-40_C28646385; SOD-882_L1.0-W0.6-RD; MPN RB161QS-40; LCSC Part C28646385
D4, D5, D7, D10: LED_1_Green; LED_0201_0603Metric; MPN XL-0201UGC; LCSC C3646922
L2: XRTC303020D4R7MBCA; IND-SMD_L3.0-W3.0_AFE303020S; MPN XRTC303020D4R7MBCA; LCSC Part C39846837
L3: FTC303020D100MBCA; IND-SMD_L3.0-W3.0_AFE303020S; MPN XRTC303020D4R7MBCA; LCSC Part C7423323
Q4: DMN1150UFB-7B; DFN-3L_L1.0-W0.6-P0.65-BR; MPN DMN1150UFB-7B; LCSC Part C459538
R27, R29, R31: 100k; R_0201_0603Metric; MPN 0201WMF1003TEE; LCSC C270364
R28: 39k; R_0201_0603Metric; MPN 0201WMF3902TEE; LCSC C473053
R30: 6.8k; R_0201_0603Metric; MPN RC0201FR-076K8L; LCSC C274877
R32: 13.7k; R_0201_0603Metric; MPN RC-01W1372FT; LCSC C320695
R33: 470R; R_0201_0603Metric; MPN 0201WMF4700TEE; LCSC C473464
R34, R40: 200R; R_0201_0603Metric; MPN 0201WMF2000TEE; LCSC C270359
R35: 10k; R_0201_0603Metric; MPN RC0201FR-0710KL; LCSC C106225
R36: 30R; R_0201_0603Metric; MPN NQ01WMJ0300TEE; LCSC C778391
U3, U4: LMR51420YFDDCR; SOT-23-6_L2.9-W1.6-P0.95-LS2.9-BL; MPN LMR51420YFDDCR; LCSC Part C7296200
U5: TPS2116DRLR; SOT-583-8_L2.1-W1.6-P0.50-LS1.6-BL; MPN TPS2116DRLR; LCSC Part C3235557
U6: NCV8187AMT180TAG; WDFN-6_L2.0-W2.0-P0.65-BL-EP; MPN NCV8187AMT180TAG; LCSC Part C893189
U7: LP5912-3.3DRVR; WSON-6-1EP_2x2mm_P0.65mm_EP1x1.6mm; MPN LP5912-3.3DRVR; LCSC C524780

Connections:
+1.8V_GYRO: C33.1, U6.5 (SNS), U6.6 (OUT); also elsewhere on the board
+5V: C30.1, C31.1, C32.1, D3.1 (C), D10.2 (A), R35.2, U5.2 (VOUT), U5.7 (VOUT), U6.1 (IN), U6.2 (EN), U7.4 (EN), U7.6 (IN); also elsewhere on the board
+5V_BUCK: C29.1, D3.2 (A), L3.2, R27.2, R31.2, R34.1, U5.3 (VIN1), U5.5 (MODE)
+5V_USB: U5.6 (VIN2); also elsewhere on the board
+10V: C28.1, L2.2, R29.2, R33.1; also elsewhere on the board
+BATT: C24.1, C25.1, D6.1 (C), U3.3 (VIN), U4.3 (VIN), U4.5 (EN); also elsewhere on the board
/POWER/1.8V_PG: Q4.1 (G), R35.1, U6.4 (PG)
/POWER/10V_ENABLE: U3.5 (EN); also elsewhere on the board
GND: C24.2, C25.2, C28.2, C29.2, C30.2, C31.2, C32.2, C33.2, C34.2, D4.1 (K), D5.1 (K), D6.2 (A), D7.1 (K), Q4.2 (S), R28.2, R30.2, R32.2, U3.1 (GND), U4.1 (GND), U5.1 (GND), U6.3 (GND), U6.7 (EP), U7.3 (GND), U7.5 (PG), U7.7 (EP); also elsewhere on the board
unnamed: D4.2 (A), R33.2
unnamed: D5.2 (A), R34.2
unnamed: D7.2 (A), R36.2
unnamed: D10.1 (K), R40.1
unnamed: Q4.3 (D), R40.2
unnamed: C26.2, U3.6 (CB)
unnamed: R29.1, R30.1, U3.4 (FB)
unnamed: C26.1, L2.1, U3.2 (SW)
unnamed: C27.2, U4.6 (CB)
unnamed: R31.1, R32.1, U4.4 (FB)
unnamed: C27.1, L3.1, U4.2 (SW)
unnamed: R27.1, R28.1, U5.4 (PR1)

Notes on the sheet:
10V (2A)
3.3V 1A MAIN LDO
FPWM version of the LMR51420YFDDCR for less output ripple at low voltage and more consistency but less efficient
1.8V 150mA LDO (high PSRR)
5V (2A)
5V Power MUX
Switches up to 4A (TPS2117) from +5V_USB or +5V_BUCK to +5V. Prefers buck over USB, threshold voltage is about 3.5V. The threshold voltage is low to prevent accidental switchover to USB during peak consumption (worst case in flight). Emergency diode for if that happens during flight.

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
